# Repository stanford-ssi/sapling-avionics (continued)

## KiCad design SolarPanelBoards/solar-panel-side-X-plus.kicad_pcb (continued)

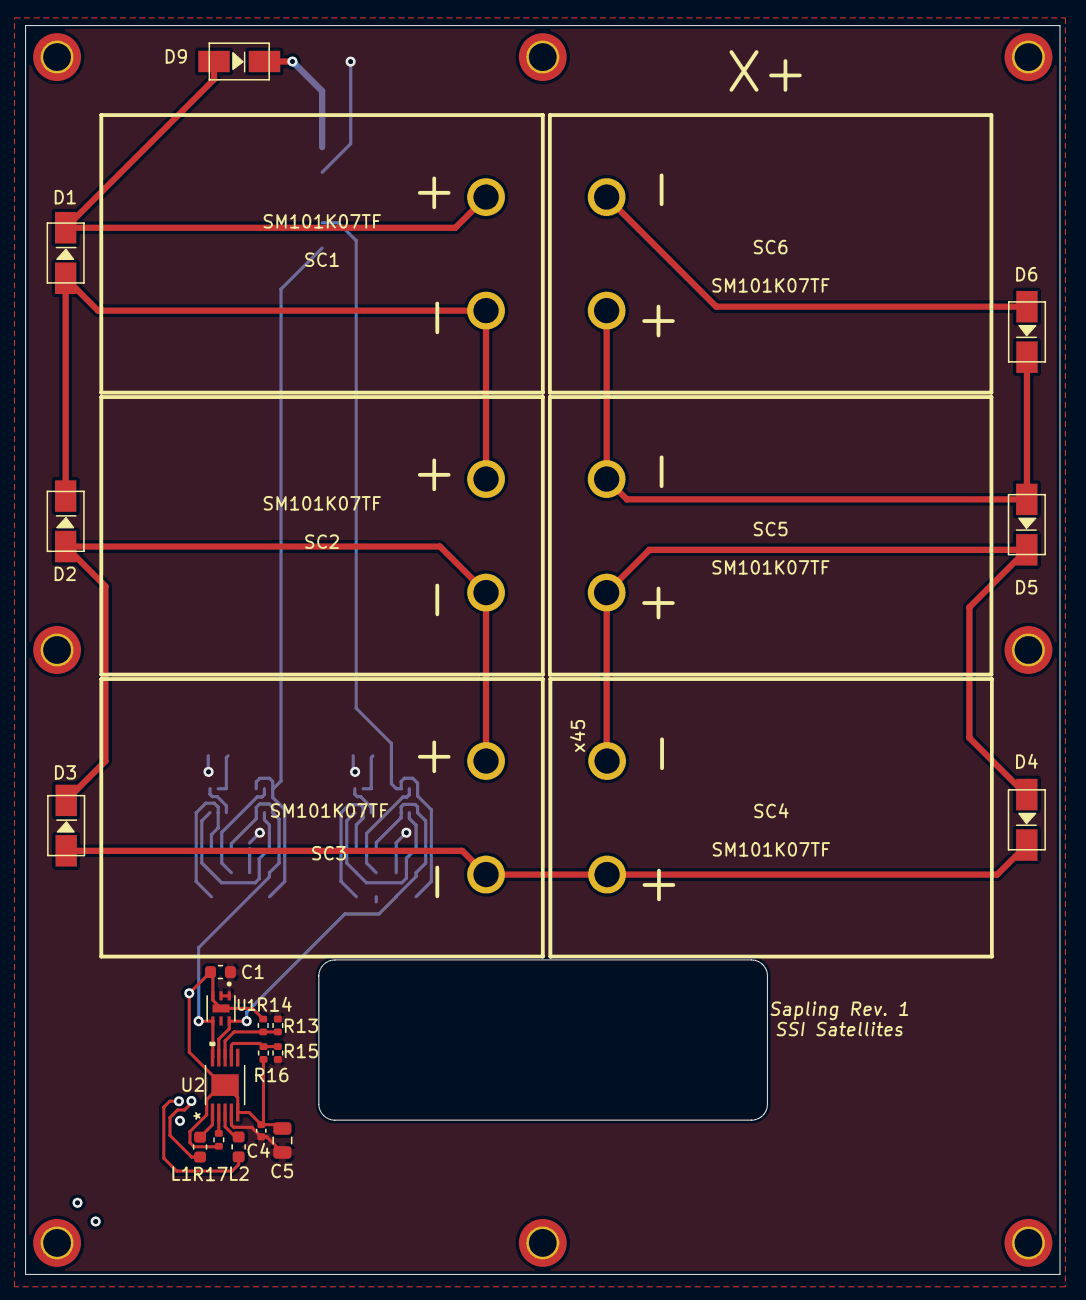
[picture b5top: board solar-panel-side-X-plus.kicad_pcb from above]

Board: 6 copper layers, 82.0 x 99.0 mm, 52 parts (1 on the bottom side), 27 nets.

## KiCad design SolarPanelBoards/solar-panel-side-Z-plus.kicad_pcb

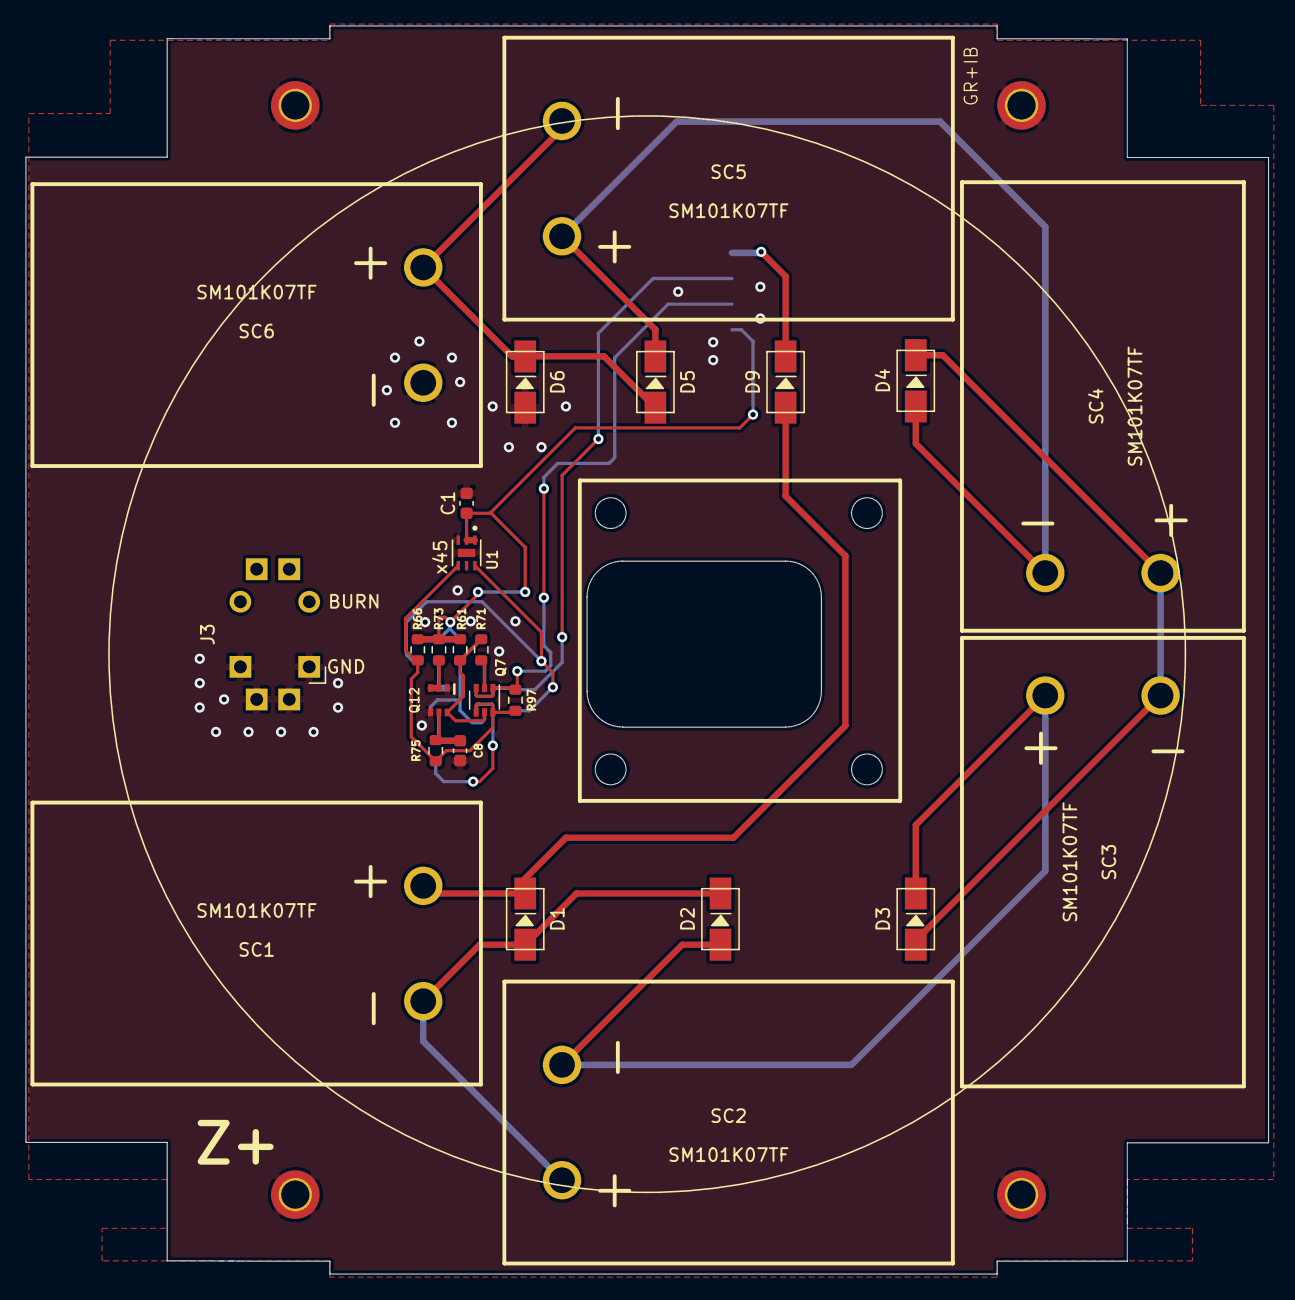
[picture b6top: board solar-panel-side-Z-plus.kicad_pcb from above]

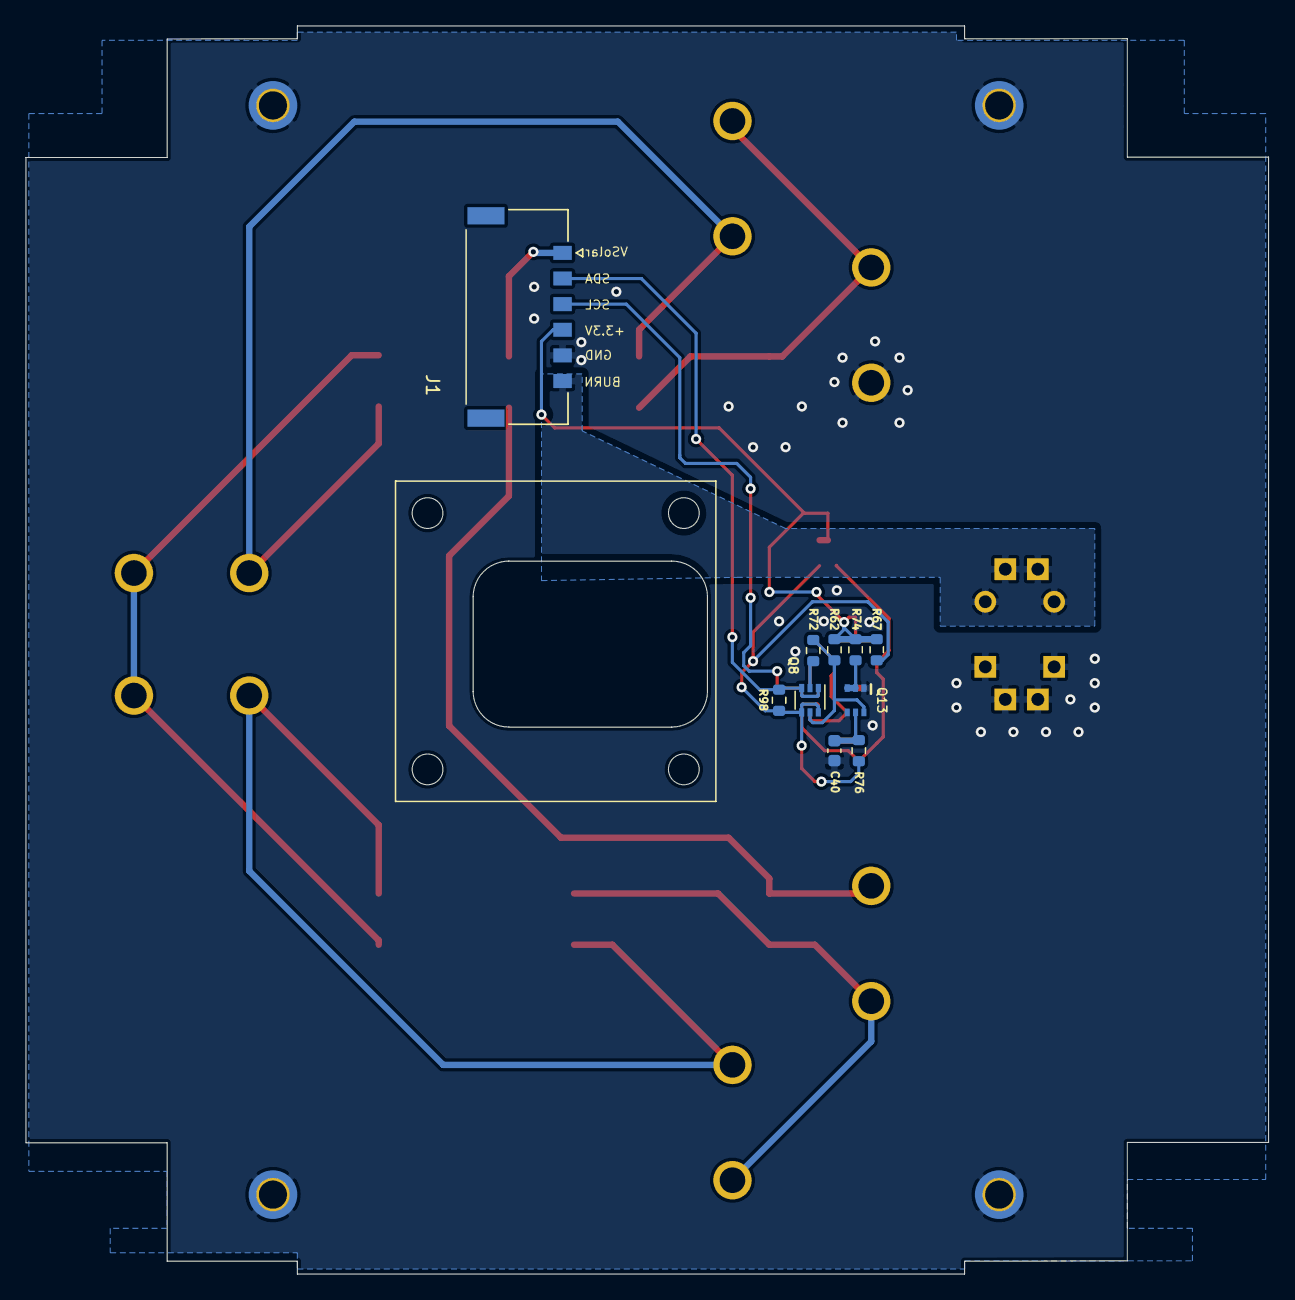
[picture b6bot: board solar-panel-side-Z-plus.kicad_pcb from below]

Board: 2 copper layers, 97.0 x 97.4 mm, 39 parts (10 on the bottom side), 22 nets.

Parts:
C1: 100nF; C_0603_1608Metric
C8, C40: 10nF; C_0603_1608Metric
D1, D2, D3, D4, D5, D6, D9: CDBA240LL-HF; DO-214AC
H3, H4, H5, H6: MountingHole_Pad; MountingHole_2.2mm_M2_DIN965_Pad_TopBottom
J1: Conn_01x06; MOLEX_2053380006
J3: Conn_01x02; Burn_Wire_Connection
Q7, Q8: MBT2222ADW1T1; SOT-363_SC-70-6
Q12, Q13: BSS138DWQ-7
R61, R62, R66, R67: 10K; R_0603_1608Metric
R71, R72: 680; R_0603_1608Metric
R73, R74: 100K; R_0603_1608Metric
R75, R76: 200K; R_0603_1608Metric
R97, R98: 0; R_0603_1608Metric
SC1, SC2, SC3, SC4, SC5, SC6: SM101K07TF
U1: OPT3001DNPT; OPT3001

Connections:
+3V3: C1.1, J1.4, R61.1, R62.1, R66.1, R67.1, R73.1, R74.1, U1.1, U1.2
BURN: J1.6, J3.2
GND: C1.2, C8.2, C40.2, D6.2, H3.1, H4.1, H5.1, H6.1, J1.5, J3.1, Q12.1, Q12.4, Q13.1, Q13.4, SC6.2, U1.3, U1.7
unnamed: C8.1, Q12.5, R75.2
unnamed: C40.1, Q13.5, R76.2
unnamed: D1.1, D9.2, SC1.1
unnamed: D1.2, D2.1, SC1.2, SC2.1
unnamed: D2.2, D3.1, SC2.2, SC3.1
unnamed: D3.2, D4.1, SC3.2, SC4.1
unnamed: D4.2, D5.1, SC4.2, SC5.1
unnamed: D5.2, D6.1, SC5.2, SC6.1
unnamed: Q7.2, R71.1
unnamed: Q8.2, R72.1
unnamed: Q12.2, Q12.3, R73.2
unnamed: Q7.5, Q12.6, R61.2, R71.2
unnamed: Q13.2, Q13.3, R74.2
unnamed: Q8.5, Q13.6, R62.2, R72.2
SCL: J1.3, Q7.1, Q7.3, R97.2
SCL_SUN: Q7.4, Q7.6, R66.2, R75.1, R97.1, U1.4
SDA: J1.2, Q8.1, Q8.3, R98.2
SDA_SUN: Q8.4, Q8.6, R67.2, R76.1, R98.1, U1.6
VSOLAR: D9.1, J1.1

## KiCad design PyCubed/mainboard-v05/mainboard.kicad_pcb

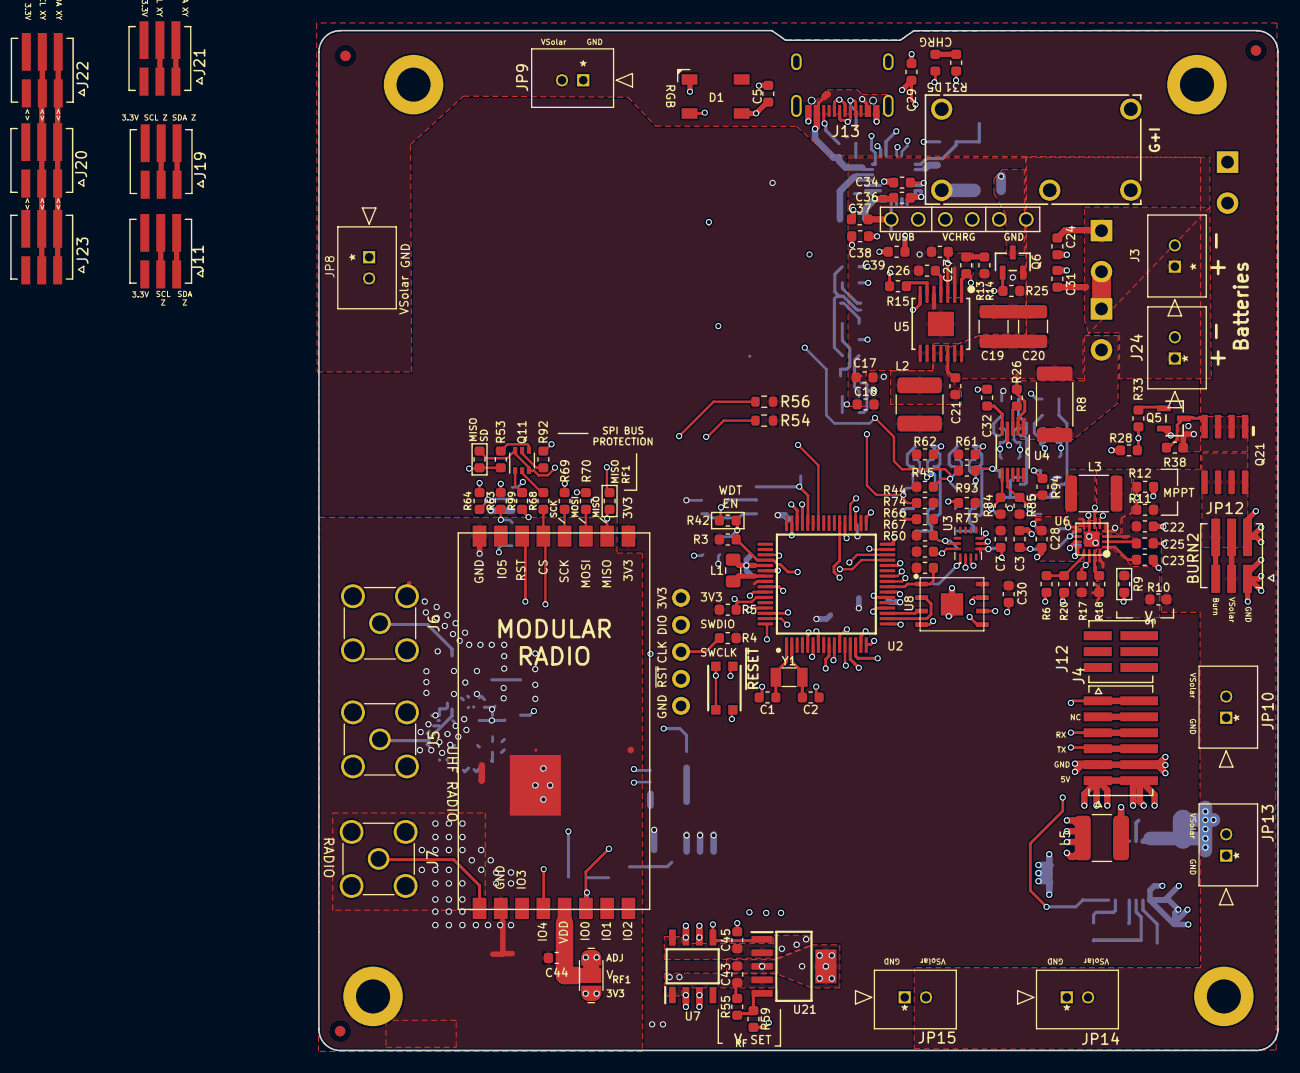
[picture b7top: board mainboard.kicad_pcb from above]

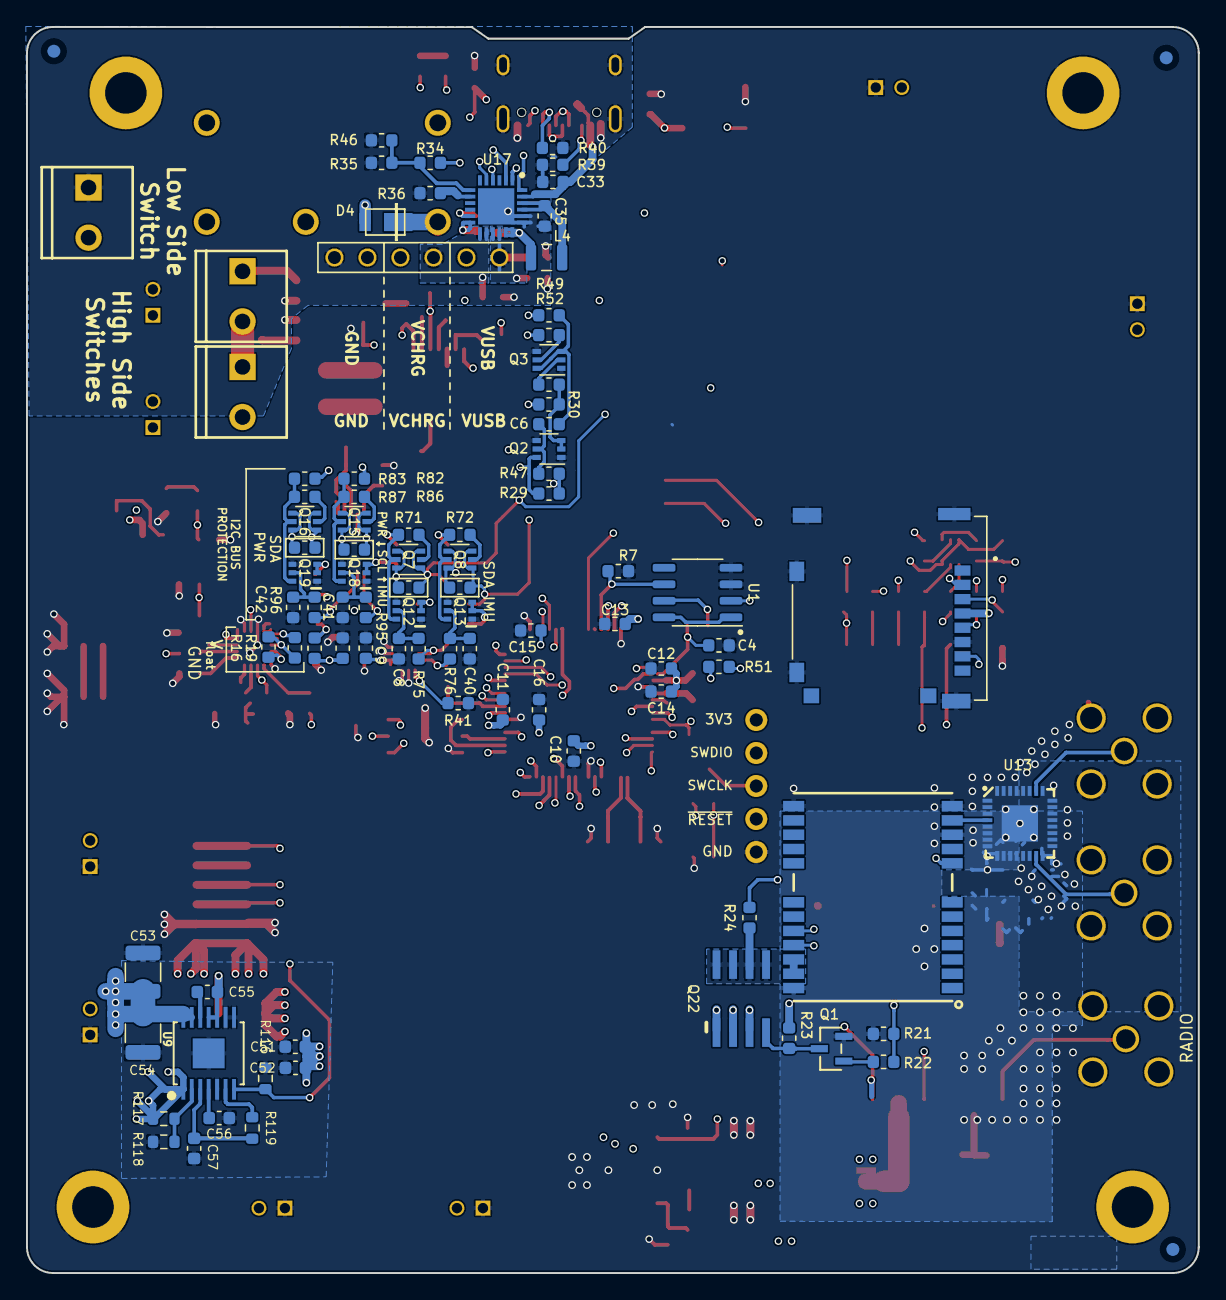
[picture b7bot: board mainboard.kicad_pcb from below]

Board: 4 copper layers, 90.2 x 95.9 mm, 221 parts (91 on the bottom side), 148 nets.

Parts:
C1, C2: 8pF; C_0603_1608Metric
C3, C5, C7, C9, C10, C11, C21, C24, C30, C45, C55: 0.1uF; C_0603_1608Metric
C4, C12, C13, C15, C27, C33, C57: 1uF; C_0603_1608Metric
C6, C14, C16, C22, C35, C39, C43, C44: 10uF; C_0603_1608Metric
C8, C40, C41, C42: 10nF; C_0603_1608Metric
C17, C18, C28, C31, C37, C38, C51, C52: 22uF; C_0603_1608Metric
C19, C20, C53, C54: 100uF; C_1210_3225Metric
C23: 2.2uF; C_0603_1608Metric
C25: 22nF; C_0603_1608Metric
C26, C32, C56: 3.3nF; C_0603_1608Metric
C29, C34: 4.7uF; C_0603_1608Metric
C36: 47nF; C_0603_1608Metric
D1: WS2812B; LED_WS2812B_PLCC4_5.0x5.0mm_P3.2mm
D4: DFLS130L; PWRDI-123
D5: GREEN LED; LED_0603_1608Metric
H1, H2, H3, H4: MountingHole_Pad; MountingHole_3.2mm_M3_DIN965_Pad
J1: 503182-1852; MOLEX_503182-1852
J2: Conn_01x05; PinHeader_1x05_P2.54mm_Vertical
J3, J24: MOLEX_Sherlock_2pos
J4: 874370643; MOLEX_874370643
J5, J6, J7: Amphenol_901-144; SMA_901-144-horizontal
J11, J12, J19, J20, J21, J22, J23: 874370343; MOLEX_874370343
J13: USB_C_pycubed; USB_C_Receptacle_XKB_U262-161N-4BVC11
J14: Conn_01x06; PinHeader_1x06_P2.54mm_Vertical
J16, J17, J18: 1985807; SCREWTERMINAL-3.5MM-2_LOCK
JP6: Jumper_3_Bridged12; SolderJumper-3_P1.3mm_Bridged12_RoundedPad1.0x1.5mm
JP8, JP9, JP10, JP13, JP14, JP15: MOLEX_Sherlock_2pos
JP12: 874370343; MOLEX_874370343
L1: 10uH; L_0805_2012Metric_Pad1.15x1.40mm_HandSolder
L2: 3.3uH; L_2141
L3: 33uH; L_1812_4532Metric
L4: 1uH; L_2510
L5: 4.7uH; L_2141
Q1, Q5: IRLML2803; SOT-23
Q2, Q3, Q7, Q8, Q15, Q16: MBT2222ADW1T1; SOT-363_SC-70-6
Q6: MMBT2222AT; SOT-23
Q11: MMDT2907; SOT-363_SC-70-6
Q12, Q13, Q18, Q19: BSS138DWQ-7
Q21, Q22: NDS8434
R1: 316K; R_0603_1608Metric
R2: 110K; R_0603_1608Metric
R3, R4, R21, R24, R31, R44, R45, R46, R52, R54, R55, R56, R61, R62, R66, R67, R82, R83, R84, R85: 10K; R_0603_1608Metric
R5, R7, R25, R28, R41, R42, R50, R51: 10k; R_0603_1608Metric
R6, R33, R92: 4.7k; R_0603_1608Metric
R8: 0.1; R_2512_6332Metric
R9: 107K; R_0603_1608Metric
R10, R53, R97, R98, R99, R101, R104, R108, R109: 0; R_0603_1608Metric
R11: 787K; R_0603_1608Metric
R12, R117: 121K; R_0603_1608Metric
R13, R29: 73.2K; R_0603_1608Metric
R14, R118: 22.1K; R_0603_1608Metric
R15, R30, R49, R73, R74, R93, R94, R119: 100K; R_0603_1608Metric
R16: 845K; R_0603_1608Metric
R17, R18, R38: 100k; R_0603_1608Metric
R19: 2.1M; R_0603_1608Metric
R20: 3.01K; R_0603_1608Metric
R22, R68: 4.7K; R_0603_1608Metric
R23, R59: 3.3K; R_0603_1608Metric
R26, R63, R64, R69, R70: 1K; R_0603_1608Metric
R34: 5.23K; R_0603_1608Metric
R35: 30.1K; R_0603_1608Metric
R36: 3.16K; R_0603_1608Metric
R39, R40: 5.1k; R_0603_1608Metric
R47, R75, R76, R95, R96: 200K; R_0603_1608Metric
R71, R72, R86, R87: 680; R_0603_1608Metric
R110: 20K; R_0603_1608Metric
R116: 300K; R_0603_1608Metric
REF1B, REF1T, REF2B, REF2T, REF3B, REF3T: Fiducial_1mm_Mask2mm
SW1: KMR231NG LFS; BTN_KMR2_4.6X2.8
U1: MAX706RESA; SO-8_3.9x4.9mm_P1.27mm
U2: ATSAMD51J19A-AU; QFP50P1200X1200X120-64N
U3: BMX160
U4: ADM1176-1ARMZ-R7
U5, U9: TPS54226PWPRPWP14_2P31X2P46-L; PWP14_2P31X2P46-L
U6: LTC4121; QFN-16-PAD
U7: KF50BD-TR; SOIC127P600X175-8N
U8: MR25H40MDF; SON127P600X500X90-9N
U13: EP2W+; QFN32-5X5MM
U14: S1216V8; S1216_24PIN_PACKAGE
U16: PE014006; RELAY_PE014006
U17: BQ25883RGER; QFN50P400X400X100-25N-D
U21: TPS7A4501DCQT
U23: RFM98PW; RFM95PW
Y1: 32.768kHz; Crystal_SMD_3215-2Pin_3.2x1.5mm

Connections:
3.3V: C5.1, C7.1, C9.2, C10.1, C11.1, C13.1, C15.1, C16.1, C17.2, C18.2, C30.1, D1.1, J1.4, J2.1, J11.3_1, J11.3_2, J19.3_1, J19.3_2, J20.3_1, J20.3_2, J21.3_1, J21.3_2, J22.3_1, J22.3_2, J23.3_1, J23.3_2, JP6.3, L2.2, Q22.1, Q22.2, Q22.3, R3.1, R4.1, R5.1, R13.2, R17.2, R18.2, R23.1, R44.1, R45.1, R50.2, R51.2, R54.1, R56.1, R61.1, R62.1, R66.1, R67.1, R73.1, R74.1, R82.1, R83.1, R84.1, R85.1, R93.1, R94.1, U1.2, U2.4, U2.8, U2.21, U2.34, U2.48, U2.56, U3.5, U3.8, U3.12, U5.1, U8.8, U23.9
5V: C51.2, C52.2, J4.1_1, J4.1_2, L5.2, R117.2, U9.1
/Avionics/BATTERY: C3.1, R1.2, R2.2, U2.15
/Avionics/XTAL1: C1.1, U2.1, Y1.1
/Avionics/XTAL2: C2.1, U2.2, Y1.2
/Burn Wires/VBURN2: JP12.3_1, JP12.3_2, Q21.5, Q21.6, Q21.7, Q21.8
/Burn Wires/VBURN_A_IN: Q21.1, Q21.2, Q21.3, R38.2, U16.11
/Power/3V3_EN: Q2.6, R29.2, U5.7
/Power/REGN: C34.1, R31.2, U17.11
/Power/V_RF: C43.2, JP6.1, R55.1, U7.1, U21.4
/RF and GPS/RF1_ANT: J7.1, U23.1
/RF and GPS/RF_IN: U13.4, U14.11
BURN_RELAY_A: Q6.1, R25.1, U2.28
ENAB_BURN2: R28.1, R33.2, U2.32
ENAB_CORAL: R116.2, U2.10, U9.7
ENAB_GPS: R21.1, R22.1, U2.62
ENAB_RF: U2.38, U7.5, U21.1
ENAB_THERM: J12.1_1, J12.1_2, U2.9
FLASH_CS: R50.1, U2.24, U8.1
FLASH_IO2: U2.19, U8.3
FLASH_IO3: U2.20, U8.7
FLASH_MISO: U2.18, U8.2
FLASH_MOSI: U2.17, U8.5
FLASH_SCK: U2.23, U8.6
GND: C1.2, C2.2, C3.2, C4.1, C5.2, C7.2, C8.2, C9.1, C10.2, C11.2, C12.1, C13.2, C14.2, C15.2, C16.2, C17.1, C18.1, C19.2, C20.2, C22.2, C23.2, C26.2, C27.2, C28.2, C30.2, C32.1, C40.2, C41.2, C42.2, C43.1, C44.1, C45.1, C51.1, C52.1, C53.2, C54.2, C56.2, C57.2, D1.3, H1.1, H2.1, H3.1, H4.1, J1.6, J1.P1, J1.P2, J1.P3, J1.P4, J1.P5, J2.5, J4.2_1, J4.2_2, J5.2, J6.2, J7.2, J12.2_1, J12.2_2, J14.5, J18.2, JP8.1, JP9.1, JP10.1, JP12.1_1, JP12.1_2, JP13.1, JP14.1, JP15.1, Q1.2, Q2.1, Q2.4, Q3.1, Q3.4, Q5.2, Q6.2, Q12.1, Q12.4, Q13.1, Q13.4, Q18.1, Q18.4, Q19.1, Q19.4, R2.1, R7.1, R9.2, R12.1, R14.1, R20.1, R21.2, R25.2, R28.2, R41.2, R59.2, R116.1, R118.1, SW1.B, SW1.B', U1.3, U1.4, U2.7, U2.22, U2.33, U2.47, U2.54, U3.2, U3.3, U3.6, U3.7, U4.4, U5.5, U5.8, U5.9, U5.15, U6.P$5, U6.P$7, U6.P$12, U6.P$17, U7.2, U7.3, U7.6, U7.7, U8.4, U8.9, U9.5, U9.8, U9.9, U9.15, U13.1, U13.2, U13.3, U13.5, U13.6, U13.7, U13.8, U13.9, U13.10, U13.11, U13.12, U13.13, U13.14, U13.16, U13.17, U13.18, U13.19, U13.20, U13.21, U13.22, U13.23, U13.24, U13.25, U13.27, U13.28, U13.29, U13.30, U13.31, U13.32, U13.EP, U14.10, U14.12, U14.13, U14.24, U16.12, U21.3, U21.6, U23.2, U23.16, U23.17
GNDREF: C24.2, C29.2, C31.2, C33.1, C34.2, C35.1, C37.1, C38.1, C39.1, J3.2, J13.A1, J13.A12, J13.S1, J14.6, J18.1, J24.2, R35.1, R36.1, R39.1, R40.1, R46.1, U17.19, U17.20, U17.25
GPS_PWR_IN: Q22.5, Q22.6, Q22.7, Q22.8, R24.2
L1_PROG: R6.1, R20.2, U6.P$13
MISO: Q11.3, Q11.6, R101.2, R104.2, U2.31
MISO_RF1: R99.2, R101.1, U23.10
MISO_SD: J1.7, R53.2, R104.1
MOSI: R64.2, R70.1, U2.29
MOSI_RF1: R70.2, U23.11
MOSI_SD: J1.3, R64.1
unnamed: C6.1, Q3.3, Q3.6, R49.2
unnamed: C6.2, Q2.5, R47.2
unnamed: C8.1, Q12.5, R75.2
unnamed: C12.2, C14.1, L1.1, U2.53
unnamed: C21.1, L2.1, U5.10, U5.11
unnamed: C21.2, U5.12
unnamed: C23.1, U6.P$1
unnamed: C25.1, U6.P$2
unnamed: C25.2, L3.2, U6.P$4
unnamed: C26.1, U5.4
unnamed: C27.1, R15.2, U5.3
unnamed: C32.2, U4.5
unnamed: C35.2, L4.1, U17.21, U17.22
unnamed: C36.1, L4.2, U17.17, U17.18
unnamed: C36.2, U17.12
unnamed: C37.2, C38.2, J14.1, U17.15, U17.16
unnamed: C39.2, J14.3, U17.13, U17.14
unnamed: C40.1, Q13.5, R76.2
unnamed: C41.1, Q18.5, R95.2
unnamed: C42.1, Q19.5, R96.2
unnamed: C55.1, L5.1, U9.10, U9.11
unnamed: C55.2, U9.12
unnamed: C56.1, U9.4
unnamed: C57.1, R119.2, U9.3
unnamed: D1.4, U2.42
unnamed: D4.A, Q6.3, U16.5
unnamed: D5.2, R31.1
unnamed: J4.5_1, J4.5_2
unnamed: J5.1, U13.15
unnamed: J6.1, U13.26
unnamed: J16.2, J17.1
unnamed: L1.2, U2.55
unnamed: L3.1, U6.P$8
unnamed: Q1.1, R22.2
unnamed: Q1.3, Q22.4, R23.2
unnamed: Q2.2, Q2.3, R30.2, R110.2
unnamed: Q3.2, R110.1
unnamed: Q3.5, R52.1
unnamed: Q5.1, R33.1
unnamed: Q7.2, R71.1
unnamed: Q8.2, R72.1
unnamed: Q11.1, R99.1
unnamed: Q11.2, R68.1
unnamed: Q11.4, R53.1
unnamed: Q11.5, R92.1
unnamed: Q12.2, Q12.3, R73.2
unnamed: Q7.5, Q12.6, R61.2, R71.2
unnamed: Q13.2, Q13.3, R74.2
unnamed: Q8.5, Q13.6, R62.2, R72.2
unnamed: Q15.2, R86.1
unnamed: Q15.5, Q18.6, R82.2, R86.2
unnamed: Q16.2, R87.1
unnamed: Q16.5, Q19.6, R83.2, R87.2
unnamed: Q18.2, Q18.3, R93.2
unnamed: Q19.2, Q19.3, R94.2
unnamed: Q5.3, Q21.4, R38.1
unnamed: R6.2, U2.16
unnamed: R9.1, R10.1, U6.P$16
unnamed: R11.1, R12.2, U6.P$6
unnamed: R13.1, R14.2, U5.2
unnamed: R15.1, U5.6
unnamed: R16.1, U6.P$11
unnamed: R16.2, R19.2, U6.P$10
unnamed: R18.1, U6.P$15
unnamed: R24.1, U14.8
unnamed: R26.2, U4.3
unnamed: R34.2, R35.2, R46.2, U17.7
unnamed: R36.2, U17.8
unnamed: R41.1, U3.1
unnamed: R42.2, U1.7
unnamed: R55.2, R59.1, U21.5
unnamed: R117.1, R118.2, U9.2
unnamed: R119.1, U9.6
unnamed: U1.1, U1.8
unnamed: U14.22, U14.23
RF1_CS: R5.2, R68.2, U2.59, U23.13
RF1_IO0: U2.6, U23.6
RF1_IO4: U2.5, U23.4
RF1_RST: U2.61, U23.14
RST_CORAL: J4.6_1, J4.6_2, U2.12
RX: U2.64, U14.20
RX_2: J4.4_1, J4.4_2, U2.14
SCK: R63.2, R69.2, U2.30
SCK_RF1: R69.1, U23.12
SCK_SD: J1.5, R63.1
SCL: J11.2_1, J11.2_2, J19.2_1, J19.2_2, Q7.1, Q7.3, Q15.1, Q15.3, R45.2, R97.2, R108.2, U2.26
SCL_2: J20.2_1, J20.2_2, J21.2_1, J21.2_2, J22.2_1, J22.2_2, J23.2_1, J23.2_2, R54.2, U2.36
SCL_IMU: Q7.4, Q7.6, R66.2, R75.1, R97.1, U3.13
SCL_PWR: Q15.4, Q15.6, R84.2, R95.1, R108.1, U4.6, U17.5
SDA: J11.1_1, J11.1_2, J19.1_1, J19.1_2, Q8.1, Q8.3, Q16.1, Q16.3, R44.2, R98.2, R109.2, U2.25
SDA_2: J20.1_1, J20.1_2, J21.1_1, J21.1_2, J22.1_1, J22.1_2, J23.1_1, J23.1_2, R56.2, U2.35
SDA_IMU: Q8.4, Q8.6, R67.2, R76.1, R98.1, U3.14
SDA_PWR: Q16.4, Q16.6, R85.2, R96.1, R109.1, U4.7, U17.4
SD_CS: J1.2, R51.1, R92.2, U2.51
SENSE_THERM: J12.3_1, J12.3_2, U2.3
STAT: D5.1, U17.2
SWCLK: J2.3, R4.2, U2.57
SWDIO: J2.2, U2.58
TX: U2.63, U14.21
TX_2: J4.3_1, J4.3_2, U2.13
USB_CC1: J13.A5, R40.2
USB_CC2: J13.B5, R39.2
USB_D+: J13.A6, J13.B6, U2.46, U17.24
USB_D-: J13.A7, J13.B7, U2.45, U17.1
VBATT: C19.1, C20.1, C28.1, C45.2, C53.1, C54.1, D4.C, J14.2, R1.1, R8.1, R19.1, R26.1, R29.1, R30.1, R47.1, R49.1, U4.2, U5.13, U5.14, U6.P$9, U7.8, U9.13, U9.14, U16.1, U16.14, U21.2
VBATT_SENSE: J17.2, R8.2, U4.1
VBUS_IN: C29.1, C33.2, J13.A4, J13.A9, R34.1, U17.23
VBUS_RESET: R52.2, U2.37
VCC_RF1: C44.2, JP6.2, U23.5
VCHRG: C24.1, C31.1, J3.1, J14.4, J16.1, J24.1
VSOLAR: C22.1, JP8.2, JP9.2, JP10.2, JP12.2_1, JP12.2_2, JP13.2, JP14.2, JP15.2, R10.2, R11.2, U6.P$3
WDT_WDI: R7.2, U1.6, U2.44
~CHRG: R17.1, U2.11, U6.P$14
~RESET: C4.2, J2.4, R3.2, R42.1, SW1.A, SW1.A', U2.52

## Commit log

2021-12-20 add initial pinout
2021-12-23 add i2c devices
2021-12-23 add coral power enable
2022-01-09 oops, GPS and coral were on the same sercom
2022-02-25 add coral enable and update thermistor pin
2022-02-28 added sapling side panels, battery boards, and pycubed
2022-03-02 add gitignore and clean up solarpanelboards
2022-03-02 re-arrange docs
2022-03-04 Added simple thermistor circuit with logic switch to activate.
2022-04-10 pa20 for thermistor enable
2022-05-01 rearranged x-minus
2022-05-05 Battery board and side panels ready for CAD check and review, pycubed not finished yet
2022-05-05 add digikey-kicad-library
2022-05-05 update sym and fp tables to use rel paths
2022-05-05 change lib and fp paths to relative
2022-05-05 add digikey-kicad-lib
2022-05-08 side panels ready except for RF trace width
2022-05-08 radio and gps moved to make space for limit switches
2022-05-08 updated schematics
2022-05-08 new coils
2022-05-08 added I2C protection PCB layout
2022-05-08 updated sch
2022-05-08 Changed outline of minus z plates to accommodate switch
2022-05-09 pycubed finished, awaiting review
2022-05-09 opps added step
2022-05-09 New X-minus board w/ magnetorquer coils and H-bridge, I2C protection circuit
2022-05-09 Z- finished, new radio traces and edges
2022-05-09 fixed edge cuts of Z+, new step file available
2022-05-09 new edges
2022-05-09 fixed edges Z+
2022-05-09 X-minus board with backside component footprints fixed
2022-05-09 Added gerbers for X-minus solar panel board
2022-05-13 Updated X-plus schematic and net
2022-05-13 Updated X-plus schematic, netlist, PCB, and gerbers
2022-05-13 changed silkscreen in X-plus PCB, updated gerbers
2022-05-19 add wire colors
2022-05-20 Y Plus solar panel steps 1-4
2022-05-22 generate pos files
2022-05-22 Y minus updates
2022-05-22 footprint for U2
2022-05-25 added html bom, needs to be formatted still
2022-07-04 porting over to kicad 6.0, pycubed is functionally done as well as battery
2022-07-14 final silkscreen and stencil edits, gerbers added for final purchase
2022-10-17 final updates after JLC i2c error
2022-11-18 Starting design of magnetorquer side panels
2022-12-10 added start of charging circuit
2022-12-27 added LT36HV circuit
2022-12-27 add replacement sensors
2022-12-27 fixed vinreg
2022-12-27 add temp sensor
2022-12-27 sponsor
2022-12-28 added inductor footprint
2022-12-28 fixed vreg stuff
2023-01-07 Finished initial Power schematic
2023-01-12 deleted extra holes in schematic
2023-01-28 ibom
2023-01-31 Final flight side panels w/ magnetorquers finished, note final board thickness of 0.031'' and updated copper weight of 0.5oz for internal layers
2023-03-24 panels ready for fixes--i2c protection lines need fix
2023-04-29 New symbol and footprint libraries
2023-05-19 added magnetorquers
